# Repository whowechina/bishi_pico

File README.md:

# Bishi Pico - Bishi Bashi Channel Style Mini Controller
[点这里可以切换到中文版](README_CN.md)

Features:
* It's small but closely replicates the feel of the arcade controller.
* Can be daisy-chained up to 4 controllers.
* Full HID light support.
* 5 color themes for the old Bishi Bashi title, the new Bishi Bashi Channel, the Love Live After School Activity, Live Sports and Sega Naomi mini games theme.
* Command line for configurations.
* All source files open.

Thanks to many respectful guys/companies who made their tools or materials free or open source (KiCad, OnShape, InkScape, Raspberry things).

Special thanks to community projects and developers.
And also these projects:
* RP_Silicon_KiCad: https://github.com/HeadBoffin/RP_Silicon_KiCad
* Type-C: https://github.com/ai03-2725/Type-C.pretty

## About the License
It's CC-NC. So DIY for yourself and for your friend for free, don't make money from it. And plagiarism that doesn’t even dare to mention the original author is not acceptable. Plase note that pooling orders and group buying for raw materials is acceptable. Selling off any leftover components without profit is also acceptable.

If you're interested in buying from me or some kind of commercial use, please contact me (Discord, QQ group, Wechat group or leave your contact in issue section).

## My Discord Invitation
https://discord.gg/M8f2PPQFEA

## My Other Projects
You can check out my other cool projects.

* Popn Pico: https://github.com/whowechina/popn_pico
* IIDX Pico: https://github.com/whowechina/iidx_pico
* IIDX Teeny: https://github.com/whowechina/iidx_teeny
* Chu Pico: https://github.com/whowechina/chu_pico
* Mai Pico: https://github.com/whowechina/mai_pico
* Diva Pico: https://github.com/whowechina/diva_pico
* AIC Pico: https://github.com/whowechina/aic_pico
* Groove Pico: https://github.com/whowechina/groove_pico
* Geki Pico: https://github.com/whowechina/geki_pico
* Musec Pico: https://github.com/whowechina/musec_pico
* Ju Pico: https://github.com/whowechina/ju_pico
* Bishi Pico: https://github.com/whowechina/bishi_pico

## **Disclaimer** ##
I made this project in my personal time without any sponsorship. I will continue to improve the project. I have done my best to ensure that everything is accurate and functional, there's always a chance that mistakes may occur. I cannot be held responsible for any loss of your time or money that may result from using this open source project. Thank you for your understanding.

## HOW TO BUILD
### PCB and Components
* Go JLCPCB and make order with the gerber zip files (latest `Production\PCB\bishi_pico_xxx.zip`), regular FR-4 board, black color, **1.6mm** thickness.

You may need to build 2 to 4 controllers for a pary. For each controller:
* 1x Rasberry Pico Pi Pico or pin-to-pin compatible clones.  
  https://www.raspberrypi.com/products/raspberry-pi-pico
* 3x USB Type-C socket (918-418K2023S40001 or KH-TYPE-C-16P)
* 16x WS2812B-3528 RGB LEDs.
* 6x WS2812B-4020 RGB LEDs (side facing).
* 1x TMAG5273A1 or TMAG5273A2, in SOT23-6.
* 4x 0603 0.1uF (0.1~1uF all fine) capacitors.
* 4x 0603 5.1kohm resistors.
* 2x JST-SH1.0 4-pin right angle SMD connectors.  
  https://www.amazon.com/Keszoox-Adapter-Connector-Surface-KS-SH1-0-SMT-R/dp/B0D793LSV2
* 1x JST-SH1.0 dual-end 4-pin cables, 50-80mm length, pin-to-pin alignment.
  The connector footprint on PCB also supports hand soldering. So if you can't find the connectors or the cables, you can solder the wires directly to the PCB.  
  RC hobby sites often have SH1.0 4P silicone cables, but with only one end connector. You can solder the other end to the PCB. It's still a good choice.
* 1x Kailh Choc v1. Choose heavy ones (70gf), I think the yellow with 70g force is the best.  
  
* 3x MX-compatible switch, I personally use Gateron POM CJ BOX.
* Optional: 6x ESD diodes, SOD-323, 3.3V bidirectional.
* This is how it looks after soldering.  

* Becareful of 2 pin holes. It's a common oversight to either forget to solder them or to leave air bubbles during the process. To avoid this, solder slowly from one side of the hole, using minimal solder wire and a generous amount of flux.  

### Test the PCB
* You can test the PCB now, put the firmware in.
* Most LEDs should light up.
* LEDs respond to the button presses.
* Bishi Pico should be recognized as a USB HID device, here's the test page.  
  https://greggman.github.io/html5-gamepad-test/
* Move a magnetic screwdriver tip close to the TMAG5273 sensor, you'll notice the corresponding axis move in the test page.

### Sensor PCB Separation
* If everthing works fine, you can cut off (or even bend and snap) the small sensor board from the main board.  

### 3D Printing
#### Printing parameters  
* PLA or PETG.
* Layer height: 0.2mm
* Wall: >= 4.
* Support: Yes, always, but only on bed and no need for bridges.
* Glue on bed: Yes, it prevents corner warping.
* Files are always in milimeter unit, not inch.

#### 1x Spinner Parts
* Keycap: `Production\3DPrint\bishi_keycap.stl`, white, 5 walls or >=90% infill. If you have multi-color system, print the 4 triangle marks on the top in gray. 
* Bearing Fixer: `Production\3DPrint\bishi_bearing_fixer.stl`, clear transparent.
* Magnet Seat: `Production\3DPrint\bishi_mag_seat.stl`, clear transparent, choose the one matches your magnet size.
* Lever: `Production\3DPrint\bishi_lever.stl`, clear transparent.
* Plase pay attention to the orientation of the parts.  

#### Housing Parts
* Base: `Production\3DPrint\bishi_base.stl`, gray, if you have multi-filament system, use special support material for nicer screw hole surface.
* Middle Support: `Production\3DPrint\bishi_support.stl`, clear transparent.
* Panel: `Production\3DPrint\bishi_panel.3mf` (use the `_insert` version if you plan to use heatset inserts), gray, print up-side-down. If you have multi-filament system, print the logo and lines in black.

#### 3x Button Seats
* Button Seat: `Production\3DPrint\bishi_button_seat.stl`, white, print upside down.

### Assembly
#### Other components needed
* 3x Chirstmas tree clear plastic balls, 30mm diameter. They come in 2 half-balls, we only need the shorter one.  
  https://www.amazon.com/Plastic-Fillable-Ornaments-Acrylic-Christmas/dp/B09ZTSGL28/
* 1x **M2.5\*6mm screws** for fixing the keycap to the bearing.
* 6x **M2\*8mm screws** for fixing the bearing and the sensor PCB to the lever.
* 6x **M3\*12mm screws** for fixing the housing parts together. If you plan to use heatset inserts, use **M3\*10mm screws** instead.
* 6x **M3\*4mm\*4mm heatset inserts**, only if you choose heatset insert version of the panel.
* 1x 6700zz (10x15x4mm) bearings for the spinner, just buy cheapest ones. They may come packed with a heavy weight oil that arrests rotation, this can be corrected by thoroughly degreasing the bearings and relubricating them with a lightweight oil like Super Lube ISO 68. For example, a soak and spin in 99% isopropyl alcohol, dry on a heated plate to remove the excess alcohol and thin and remaining grease, then a final wash in acetone (if you have all-metal bearings) and additional heated dry before relubricating will ensure the bearings spin freely.
  https://www.amazon.com/uxcell-6700ZZ-Groove-Bearings-Shielded/dp/B082PPYZQX/
* 1x round magnet, 5mm diameter (4mm also works if you stick it well), 1.5mm or 2mm tall, MUST be radially/diametrically magnetized (N-S poles on the curved side).  
  https://wargameportal.com/products/special-diametrically-magnetized-50pcs-5mm-x-2mm-3-16-x-1-16-disc-magnets?variant=49014932209942
* 1x 25mm length 2mm diameter steel shafts for the lever.  
  https://www.walmart.com/ip/Unique-Bargains-RC-Toy-Car-Frame-Part-Stainless-Steel-Round-Rod-Shaft-25mm-x-2mm-40-Pcs/108734138?wmlspartner=wlpa&selectedSellerId=571
* Some good tape (such as acetate tape or high-temp teflon tape) to fix the magnets in place.
* PTFE or UHMW tape for the sliding surfaces.
* Silicone anti-slip pads (12mm diameter, 2-3mm thickness) for the bottom.  
  
* Clear soft/flexible glue or UV curing glue. WARNING: Avoid using any cyanoacrylate-based glue, such as 502. Any glue with a similar smell should also be avoided, as they will leave white smoke marks on the acrylic.
* Optional but good to have: plastic washer (ring pads), 0.5mm thick, 2.1~2.5mm inner diameter, 5-10mm outer diameter.  
  https://www.amazon.com/Bclla-Zkenshan-washers-Shock-Proof-Leak-Proof-Insulation/dp/B091Y7H9NX/

#### Steps
1. We'll make 3 dome buttons first. Just glue the shorter half of the clear plastic ball onto the button seat use the glue mentioned earlier.  

2. Now the spinner part. Insert the bearing into the bearing fixer while keeping the components warm. You can use a hair dryer to heat them up a little. Then screw the lever and the bearing fixer together using M2 screws. Then screw the keycap to the bearing using the M2.5 screw and the magnet seat. Screw very very slowly so it won't heat up and break the 3D printed parts. Put the magnet into the magnet seat and fix it with tape. Lastly put in the shaft steel into the lever. You may also look at the Musec Pico (https://github.com/whowechina/musec_pico) for spinner assembly.  

3. Connect the SH1.0 cable to the sensor PCB. And mount the PCB and the lever to the base. A pair of plastic washer will be helpful to prevent the lever from moving. They can also be used to adjust the lever position, compensating for the printing tolerance.  

4. Connect the other side of the SH1.0 cable to the mainboard and put all 3 dome buttons and the support part on. We're almost there. Connect to a PC and do a final test before we screw the panel.  

5. Install the panel using M3 screws. Put anti-slip pads on the bottom, right on top of the screws.

#### Caution
* Each 3D printer and filament has its own tolerance. If you find the stem holes on the button are too tight, use some needle or knife to enlarge them a little bit.
* Screws are easy to break the 3D printed parts. So don't screw them too fast or too tight. When you notice the resistance suddenly increases, stop screwing.

### Firmware
* UF2 file is in `Production\Firmware` folder.
* For the new build, hold the BOOTSEL button while connect the USB to a PC, there will be a disk named "RPI-RP2" showed up. Drag the UF2 firmware binary file into it. That's it. There's a small hole at the bottom side of the Bishi Pico, it is facing right to the BOOTSEL button.
* If it's already running Bishi Pico firmware, you can either use "update" in command line or hold down all 4 buttons while connecting to USB to enter update mode.
* To access the command line, you can use this Web Serial Terminal to connect to the command line port of the controller. (Note: "?" is for help)  
  https://googlechromelabs.github.io/serial-terminal/

### Usage
* It's very simple. Just plug it in and play.
* The top type-C port is for USB connection. The left one is for daisy-chaining uplink, the right one is for daisy-chaining downlink.
* When in the daisy-chain, each controller will identify itself and change its cab color correspondingly. The first one that connects to the PC is the master (P1).
* Connect USB while pressing buttons to enter certain game theme.
  * Spinner: Bishi Bashi Channel theme;
  * Middle button: the old Bishi Bashi theme;
  * Left + Right buttons: Love Live theme;
  * Right button: Live Sports theme;
  * Left button: Sega Naomi mini games theme;

* You can set spin sensivity by "spin rate" command.
* You can set spin direction by "spin <normal|reverse>" command.
* You can set the LED brightness by "level" command.
* Other than the spin direction, all settings are synced from the master to downstream controllers in the chain.

## CAD Source File
I'm using OnShape free subscription. It's powerful but it can't archive original designs to local, so I can only share the link here. STL/DXF/DWG files are exported from this online document.  
  https://cad.onshape.com/documents/6f83a021410e82d07cc15922/w/bf90a7bd098b65b3b6359caa/e/e7d515c69c3b65443d3da058

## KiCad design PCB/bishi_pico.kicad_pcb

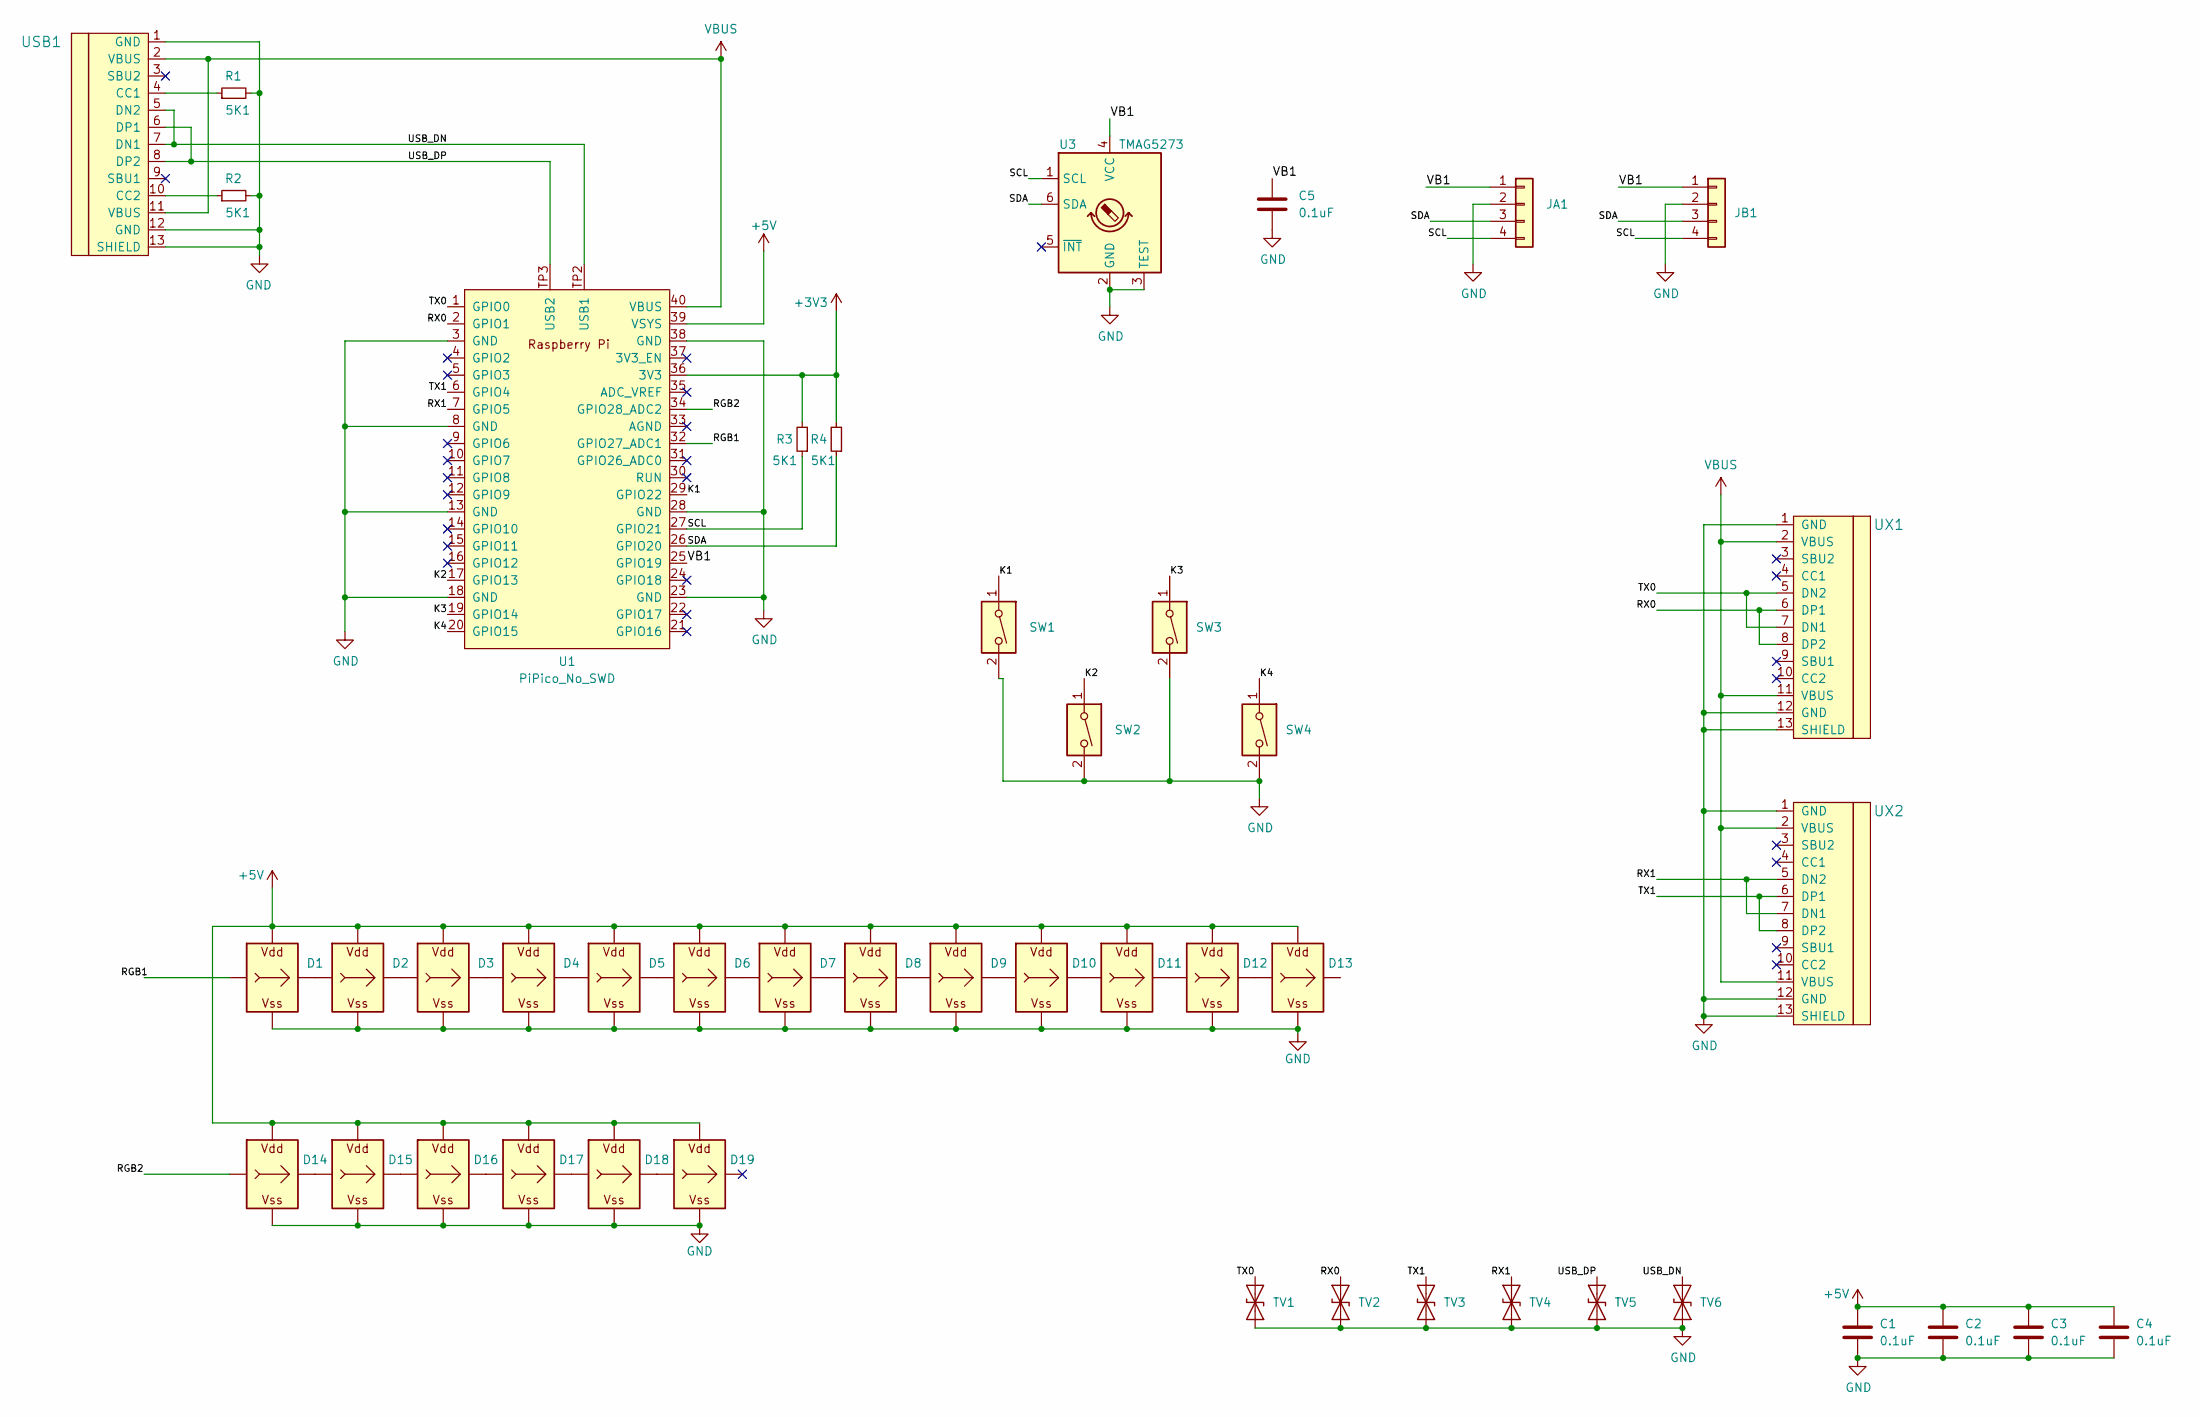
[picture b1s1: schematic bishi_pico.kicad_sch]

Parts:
C1, C2, C3, C4, C5: 0.1uF; C_0603_1608Metric_Pad1.08x0.95mm_HandSolder
D1, D2, D3, D4, D5, D6, D7, D8, D9, D10, D11, D12, D13: WS2812B_Unified; WS2812B-2835
D14, D15, D16, D17, D18, D19: WS2812B_Unified; WS2812B-4020
JA1: Conn_01x04; SH1.0_4P_Solder_Combo
JB1: Conn_01x04; SH1.0_4P_Solder_Combo
R1, R2, R3, R4: 5K1; R_0603_1608Metric_Pad0.98x0.95mm_HandSolder; LCSC C23186
SW1: SW_DIP_x01; SW_Kailh_Choc_V1V2_1.00u_LED
SW2, SW3, SW4: SW_DIP_x01; Cherry_MX
TV1, TV2, TV3, TV4, TV5, TV6: ESD9B3.3ST5G; D_SOD-323_HandSoldering
U1: PiPico_No_SWD; RPi_Pico_SMD_Pins_No_SWD
U3: TMAG5273; TSOT-23-6_HandSoldering
USB1: U262-161N-4BVC11; HRO-TYPE-C-31-M-12-Assembly; LCSC C319148
UX1, UX2: U262-161N-4BVC11; HRO-TYPE-C-31-M-12-Assembly; LCSC C319148

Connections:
+3V3: R3.2, R4.2, U1.36 (3V3)
+5V: C1.1, C2.1, C3.1, C4.1, D1.V (VDD), D2.V (VDD), D3.V (VDD), D4.V (VDD), D5.V (VDD), D6.V (VDD), D7.V (VDD), D8.V (VDD), D9.V (VDD), D10.V (VDD), D11.V (VDD), D12.V (VDD), D13.V (VDD), D14.V (VDD), D15.V (VDD), D16.V (VDD), D17.V (VDD), D18.V (VDD), D19.V (VDD), U1.39 (VSYS)
/K1: SW1.1, U1.29 (GPIO22)
/K2: SW2.1, U1.17 (GPIO13)
/K3: SW3.1, U1.19 (GPIO14)
/K4: SW4.1, U1.20 (GPIO15)
/RGB1: D1.I (In), U1.32 (GPIO27_ADC1)
/RGB2: D14.I (In), U1.34 (GPIO28_ADC2)
/RX0: TV2.1 (A1), U1.2 (GPIO1), UX1.6 (DP1), UX1.8 (DP2)
/RX1: TV4.1 (A1), U1.7 (GPIO5), UX2.5 (DN2), UX2.7 (DN1)
/SCL: JA1.4, JB1.4, R3.1, U1.27 (GPIO21), U3.1 (SCL)
/SDA: JA1.3, JB1.3, R4.1, U1.26 (GPIO20), U3.6 (SDA)
/TX0: TV1.1 (A1), U1.1 (GPIO0), UX1.5 (DN2), UX1.7 (DN1)
/TX1: TV3.1 (A1), U1.6 (GPIO4), UX2.6 (DP1), UX2.8 (DP2)
/USB_DN: TV6.1 (A1), U1.TP2 (USB1), USB1.5 (DN2), USB1.7 (DN1)
/USB_DP: TV5.1 (A1), U1.TP3 (USB2), USB1.6 (DP1), USB1.8 (DP2)
/VB1: C5.1, JA1.1, JB1.1, U1.25 (GPIO19), U3.4 (VCC)
GND: C1.2, C2.2, C3.2, C4.2, C5.2, D1.G (VSS), D2.G (VSS), D3.G (VSS), D4.G (VSS), D5.G (VSS), D6.G (VSS), D7.G (VSS), D8.G (VSS), D9.G (VSS), D10.G (VSS), D11.G (VSS), D12.G (VSS), D13.G (VSS), D14.G (VSS), D15.G (VSS), D16.G (VSS), D17.G (VSS), D18.G (VSS), D19.G (VSS), JA1.2, JB1.2, R1.2, R2.2, SW1.2, SW2.2, SW3.2, SW4.2, TV1.2 (A2), TV2.2 (A2), TV3.2 (A2), TV4.2 (A2), TV5.2 (A2), TV6.2 (A2), U1.3 (GND), U1.8 (GND), U1.13 (GND), U1.18 (GND), U1.23 (GND), U1.28 (GND), U1.38 (GND), U3.2 (GND), U3.3 (TEST), USB1.1 (GND), USB1.12 (GND), USB1.13 (SHIELD), UX1.1 (GND), UX1.12 (GND), UX1.13 (SHIELD), UX2.1 (GND), UX2.12 (GND), UX2.13 (SHIELD)
unnamed: D1.O (Out), D2.I (In)
unnamed: D2.O (Out), D3.I (In)
unnamed: D3.O (Out), D4.I (In)
unnamed: D4.O (Out), D5.I (In)
unnamed: D5.O (Out), D6.I (In)
unnamed: D6.O (Out), D7.I (In)
unnamed: D7.O (Out), D8.I (In)
unnamed: D8.O (Out), D9.I (In)
unnamed: D9.O (Out), D10.I (In)
unnamed: D10.O (Out), D11.I (In)
unnamed: D11.O (Out), D12.I (In)
unnamed: D12.O (Out), D13.I (In)
unnamed: D14.O (Out), D15.I (In)
unnamed: D15.O (Out), D16.I (In)
unnamed: D16.O (Out), D17.I (In)
unnamed: D17.O (Out), D18.I (In)
unnamed: D18.O (Out), D19.I (In)
unnamed: R1.1, USB1.4 (CC1)
unnamed: R2.1, USB1.10 (CC2)
VBUS: U1.40 (VBUS), USB1.2 (VBUS), USB1.11 (VBUS), UX1.2 (VBUS), UX1.11 (VBUS), UX2.2 (VBUS), UX2.11 (VBUS)

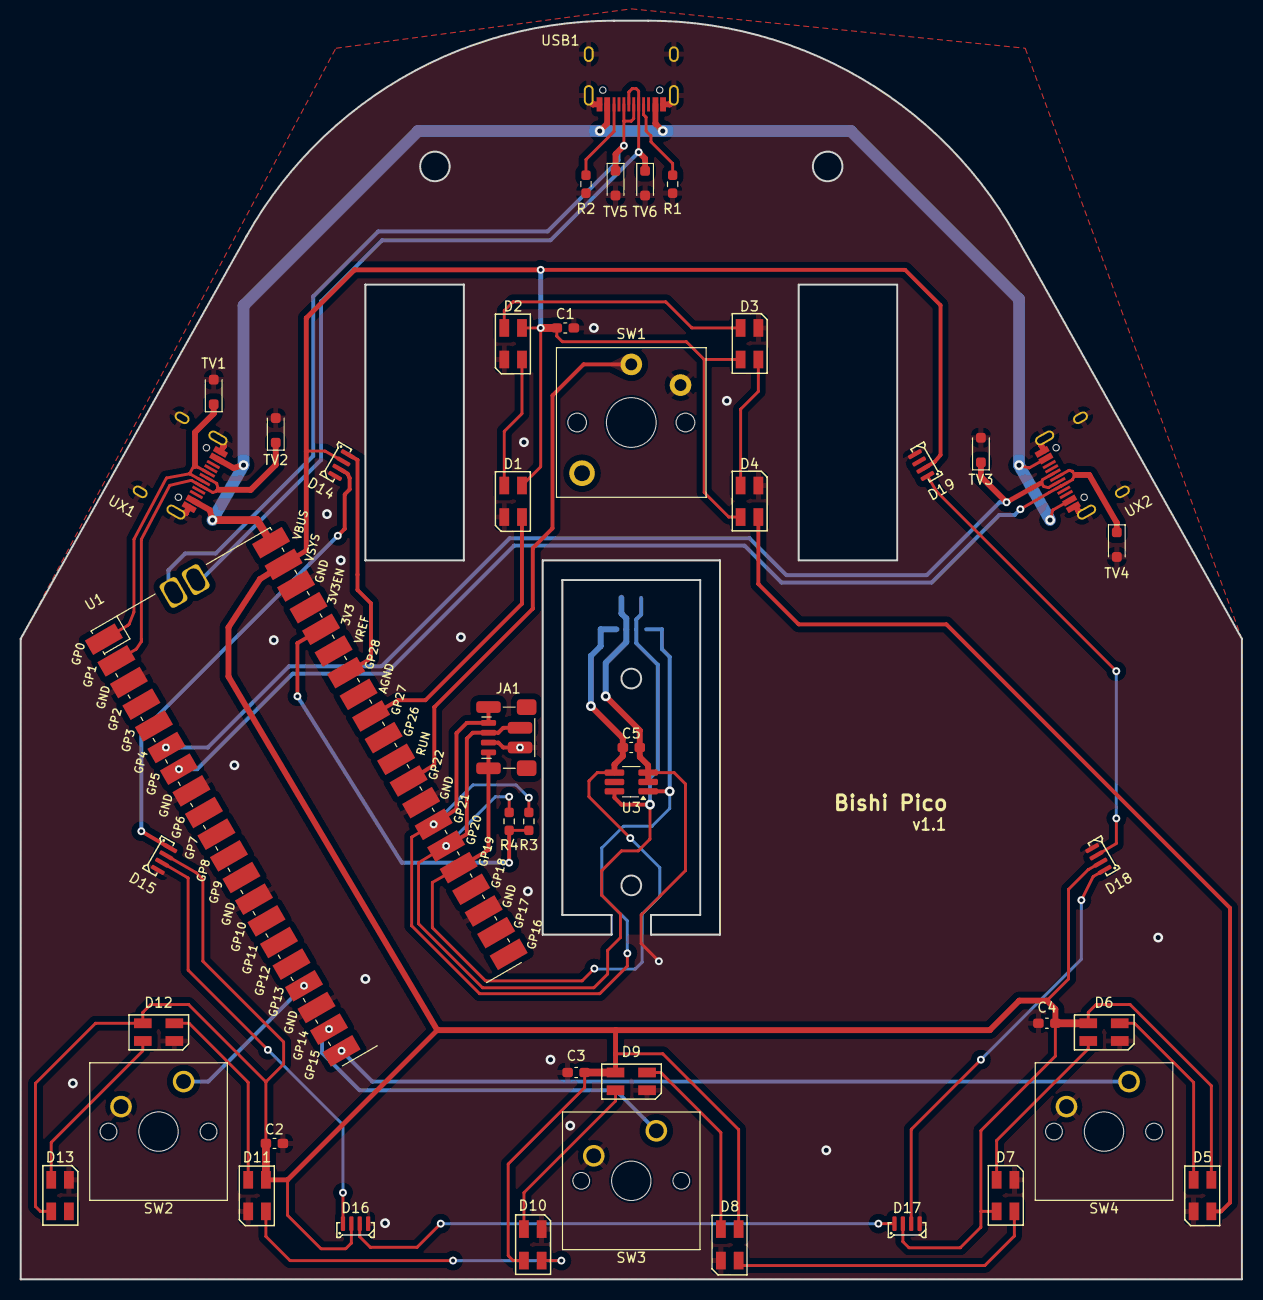
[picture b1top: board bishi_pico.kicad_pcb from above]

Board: 2 copper layers, 124.0 x 127.8 mm, 45 parts (1 on the bottom side), 38 nets.

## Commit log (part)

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2024-11-27 PCB project
2024-11-27 Reference pictures
2024-11-27 PCB v1.0
2024-11-27 CAD files for logo
2024-11-27 Firmware starts
2024-11-29 Updated logo for housing
2024-11-29 PCB v1.1 (ESD diodes added)
2024-12-01 Fix getchar return handling
2024-12-01 New cmake import script
2024-12-03 Firmware works
2024-12-03 Spin rate over sync message
2024-12-11 A new theme for LoveLive
2024-12-11 Theme color based on HSV
2024-12-12 Cons share same serial number
2024-12-17 Ready to publish
2024-12-17 Minor fix in README
2025-01-01 Fix minor markdown format issue
2025-01-04 Better polling rate
2025-02-09 Strengthen housing parts
